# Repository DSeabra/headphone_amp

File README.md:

# headphone_amp
Guitar Headphone Amp

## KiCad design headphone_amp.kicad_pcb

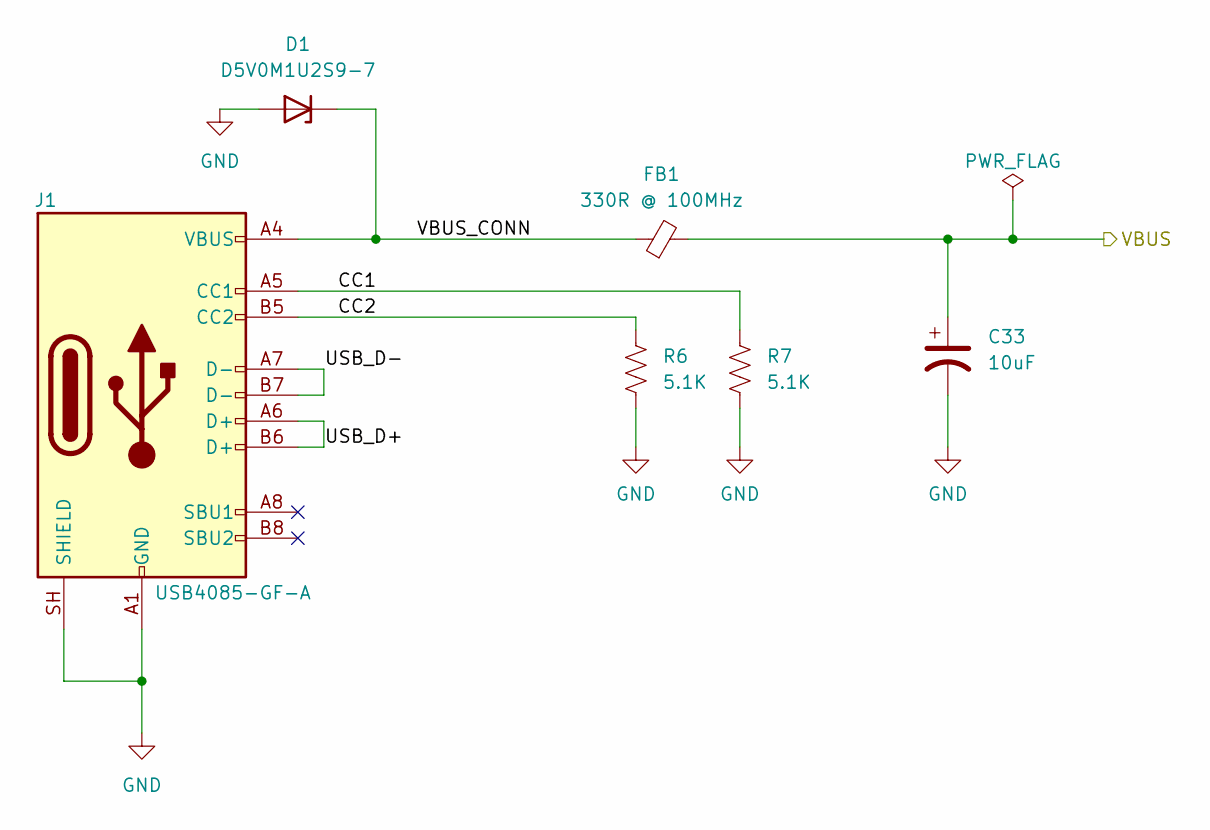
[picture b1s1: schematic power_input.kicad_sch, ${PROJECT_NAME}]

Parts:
C33: 10uF; TCJA_AVX
D1: D5V0M1U2S9-7; D_SOD-923
FB1: 330R @ 100MHz; L_0402_1005Metric
J1: USB4085-GF-A; USB_C_Receptacle_GCT_USB4085
R6, R7: 5.1K; R_0402_1005Metric

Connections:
/Power Input/CC1: J1.A5 (CC1), R7.1
/Power Input/CC2: J1.B5 (CC2), R6.1
/Power Input/USB_D+: J1.A6 (D+), J1.B6 (D+)
/Power Input/USB_D-: J1.A7 (D-), J1.B7 (D-)
/Power Input/VBUS_CONN: D1.1 (K), FB1.1, J1.A4 (VBUS), J1.A9 (VBUS), J1.B4 (VBUS), J1.B9 (VBUS)
/V_{BUS}: C33.1, FB1.2; also elsewhere on the board
GND: C33.2, D1.2 (A), J1.A1 (GND), J1.A12 (GND), J1.B1 (GND), J1.B12 (GND), J1.SH (SHIELD), R6.2, R7.2; also elsewhere on the board

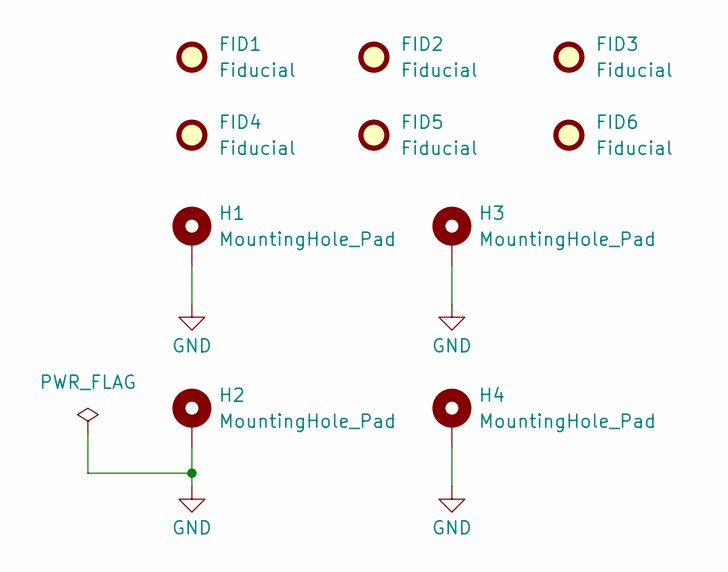
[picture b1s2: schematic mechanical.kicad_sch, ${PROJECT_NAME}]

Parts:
FID1, FID2, FID3, FID4, FID5, FID6: Fiducial; Fiducial_1.5mm_Mask3mm
H1, H2, H3, H4: MountingHole_Pad; MountingHole_3.2mm_M3_DIN965_Pad

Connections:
GND: H1.1 (1_1), H2.1 (1_1), H3.1 (1_1), H4.1 (1_1); also elsewhere on the board

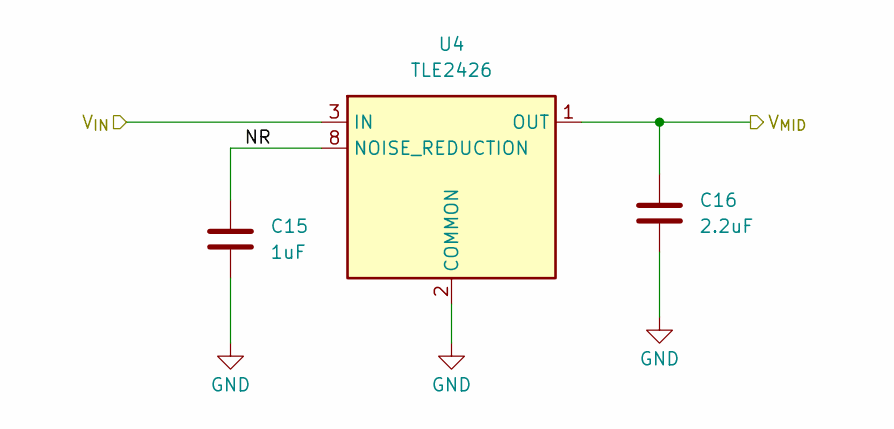
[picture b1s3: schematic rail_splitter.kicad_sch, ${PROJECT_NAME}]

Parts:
C15: 1uF; C_0603_1608Metric
C16: 2.2uF; C_0603_1608Metric
U4: TLE2426; SOIC-8_3.9x4.9mm_P1.27mm

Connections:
/Rail Splitter/NR: C15.2, U4.8 (NOISE_REDUCTION)
/V+: U4.3 (IN); also elsewhere on the board
/V_{MID}: C16.2, U4.1 (OUT); also elsewhere on the board
GND: C15.1, C16.1, U4.2 (COMMON); also elsewhere on the board

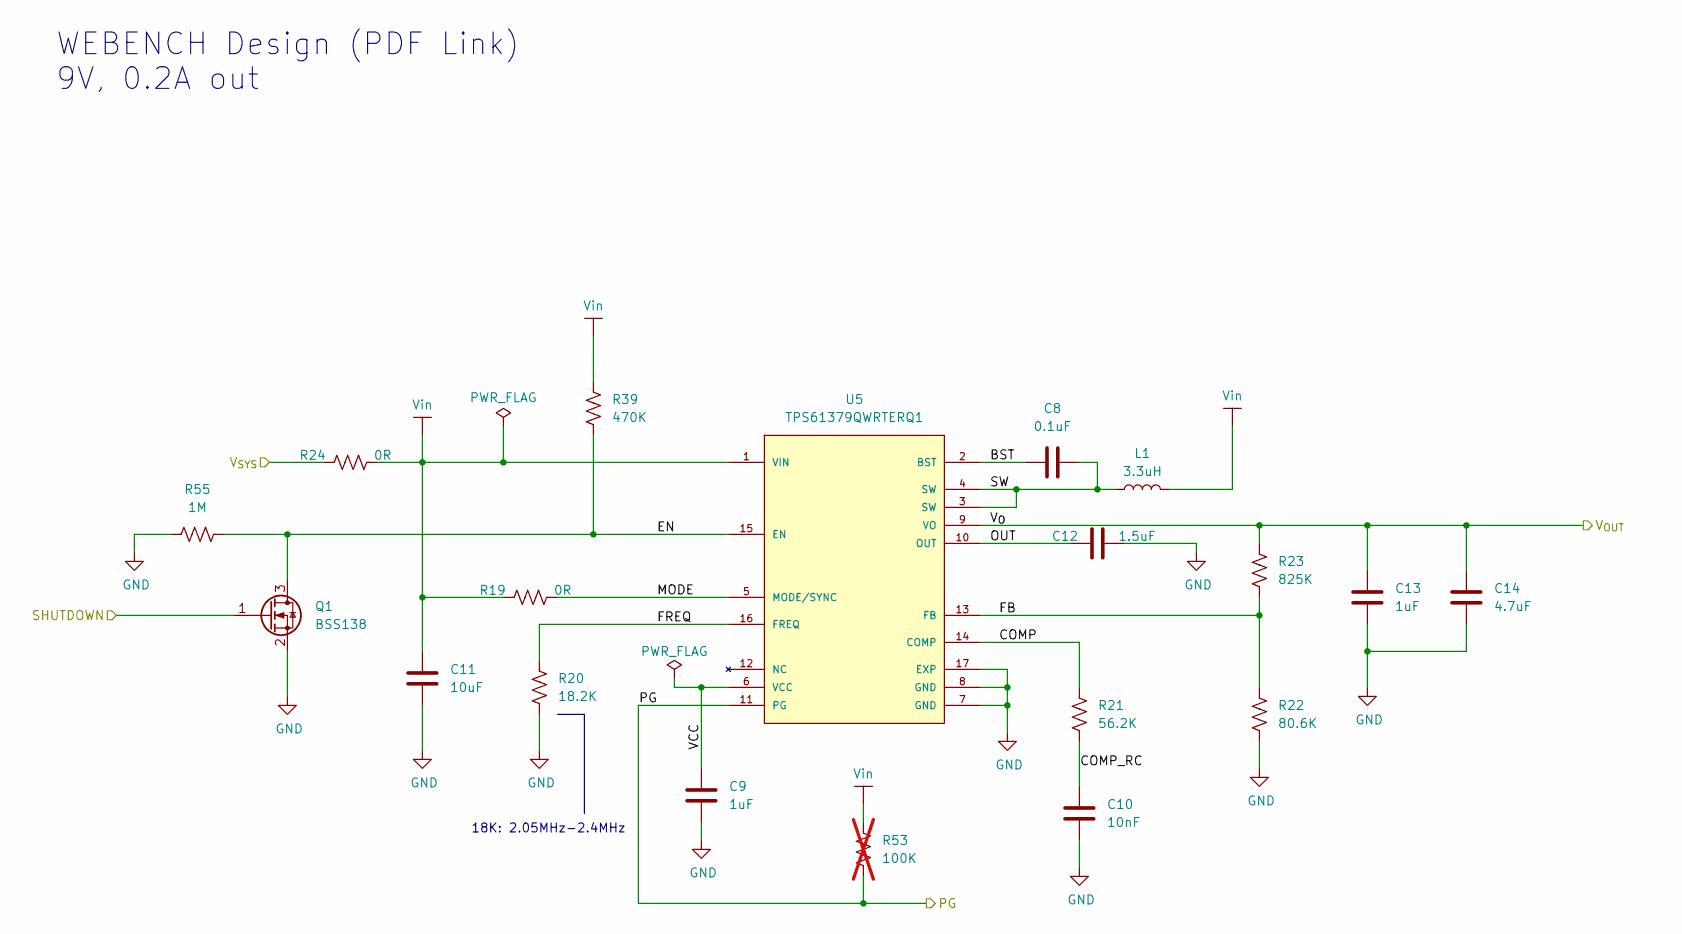
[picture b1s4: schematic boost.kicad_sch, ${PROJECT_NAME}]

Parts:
C8: 0.1uF; C_0402_1005Metric
C9, C13: 1uF; C_0402_1005Metric
C10: 10nF; C_0402_1005Metric
C11: 10uF; C_0805_2012Metric
C12: 1.5uF; C_0805_2012Metric
C14: 4.7uF; C_0603_1608Metric
L1: 3.3uH; L_1008_2520Metric
Q1: BSS138; SOT-23
R19, R24: 0R; R_0402_1005Metric
R20: 18.2K; R_0402_1005Metric
R21: 56.2K; R_0402_1005Metric
R22: 80.6K; R_0402_1005Metric
R23: 825K; R_0402_1005Metric
R39: 470K; R_0402_1005Metric
R53: 100K; R_0402_1005Metric; not fitted
R55: 1M; R_0402_1005Metric
U5: TPS61379QWRTERQ1; VREG_TPS61379QWRTERQ1

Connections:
/Boost/BST: C8.1, U5.2 (BST)
/Boost/COMP: R21.2, U5.14 (COMP)
/Boost/COMP_RC: C10.1, R21.1
/Boost/EN: Q1.3 (D), R39.2, R55.2, U5.15 (EN)
/Boost/FB: R22.2, R23.1, U5.13 (FB)
/Boost/FREQ: R20.2, U5.16 (FREQ)
/Boost/MODE: R19.2, U5.5 (MODE/SYNC)
/Boost/OUT: C12.1, U5.10 (OUT)
/Boost/PG: R53.1, U5.11 (PG); also elsewhere on the board
/Boost/SHUTDOWN: Q1.1 (G); also elsewhere on the board
/Boost/SW: C8.2, L1.1, U5.3 (SW), U5.4 (SW)
/Boost/VCC: C9.1, U5.6 (VCC)
/Boost/Vin: C11.2, L1.2, R19.1, R24.2, R39.1, R53.2, U5.1 (VIN)
/V+: C13.2, C14.2, R23.2, U5.9 (VO); also elsewhere on the board
/V_{SYS}: R24.1; also elsewhere on the board
GND: C9.2, C10.2, C11.1, C12.2, C13.1, C14.1, Q1.2 (S), R20.1, R22.1, R55.1, U5.7 (GND), U5.8 (GND), U5.17 (EXP); also elsewhere on the board

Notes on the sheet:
WEBENCH Design (PDF Link) 9V, 0.2A out
18K: 2.05MHz-2.4MHz

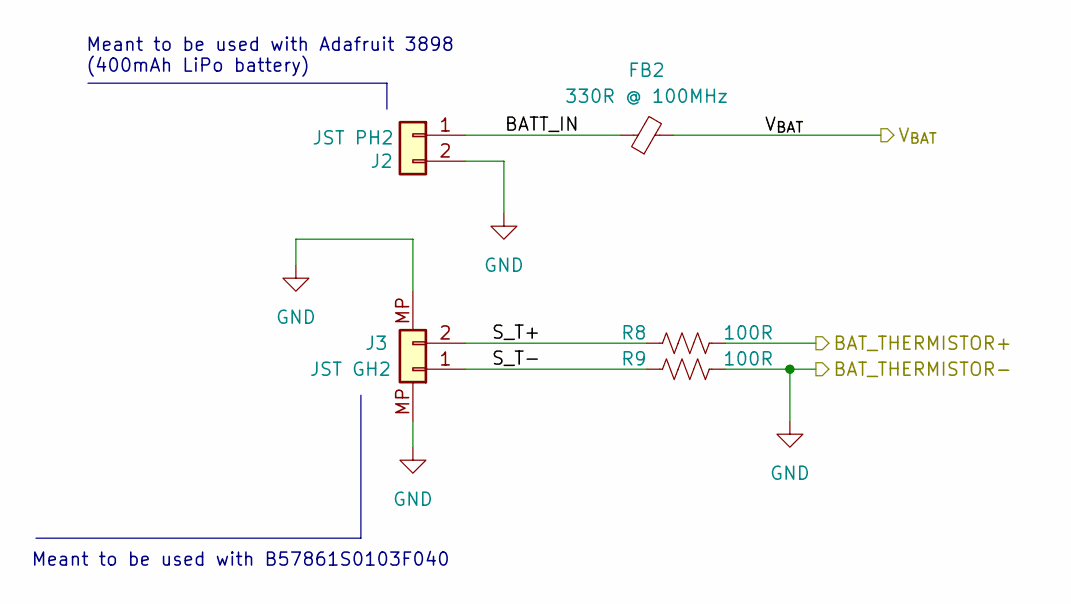
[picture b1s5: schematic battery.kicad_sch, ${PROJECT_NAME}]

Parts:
FB2: 330R @ 100MHz; L_0402_1005Metric
J2: JST PH2; JST_PH_S2B-PH-K_1x02_P2.00mm_Horizontal
J3: JST GH2; JST_GH_SM02B-GHS-TB_1x02-1MP_P1.25mm_Horizontal
R8, R9: 100R; R_0402_1005Metric

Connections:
/Battery Charger/TS+: R8.2; also elsewhere on the board
/Battery/BATT_IN: FB2.1, J2.1
/Battery/S_T+: J3.2, R8.1
/Battery/S_T-: J3.1, R9.1
/V_{BAT}: FB2.2; also elsewhere on the board
GND: J2.2, J3.MP, R9.2; also elsewhere on the board

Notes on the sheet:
Meant to be used with B57861S0103F040
Meant to be used with Adafruit 3898 (400mAh LiPo battery)

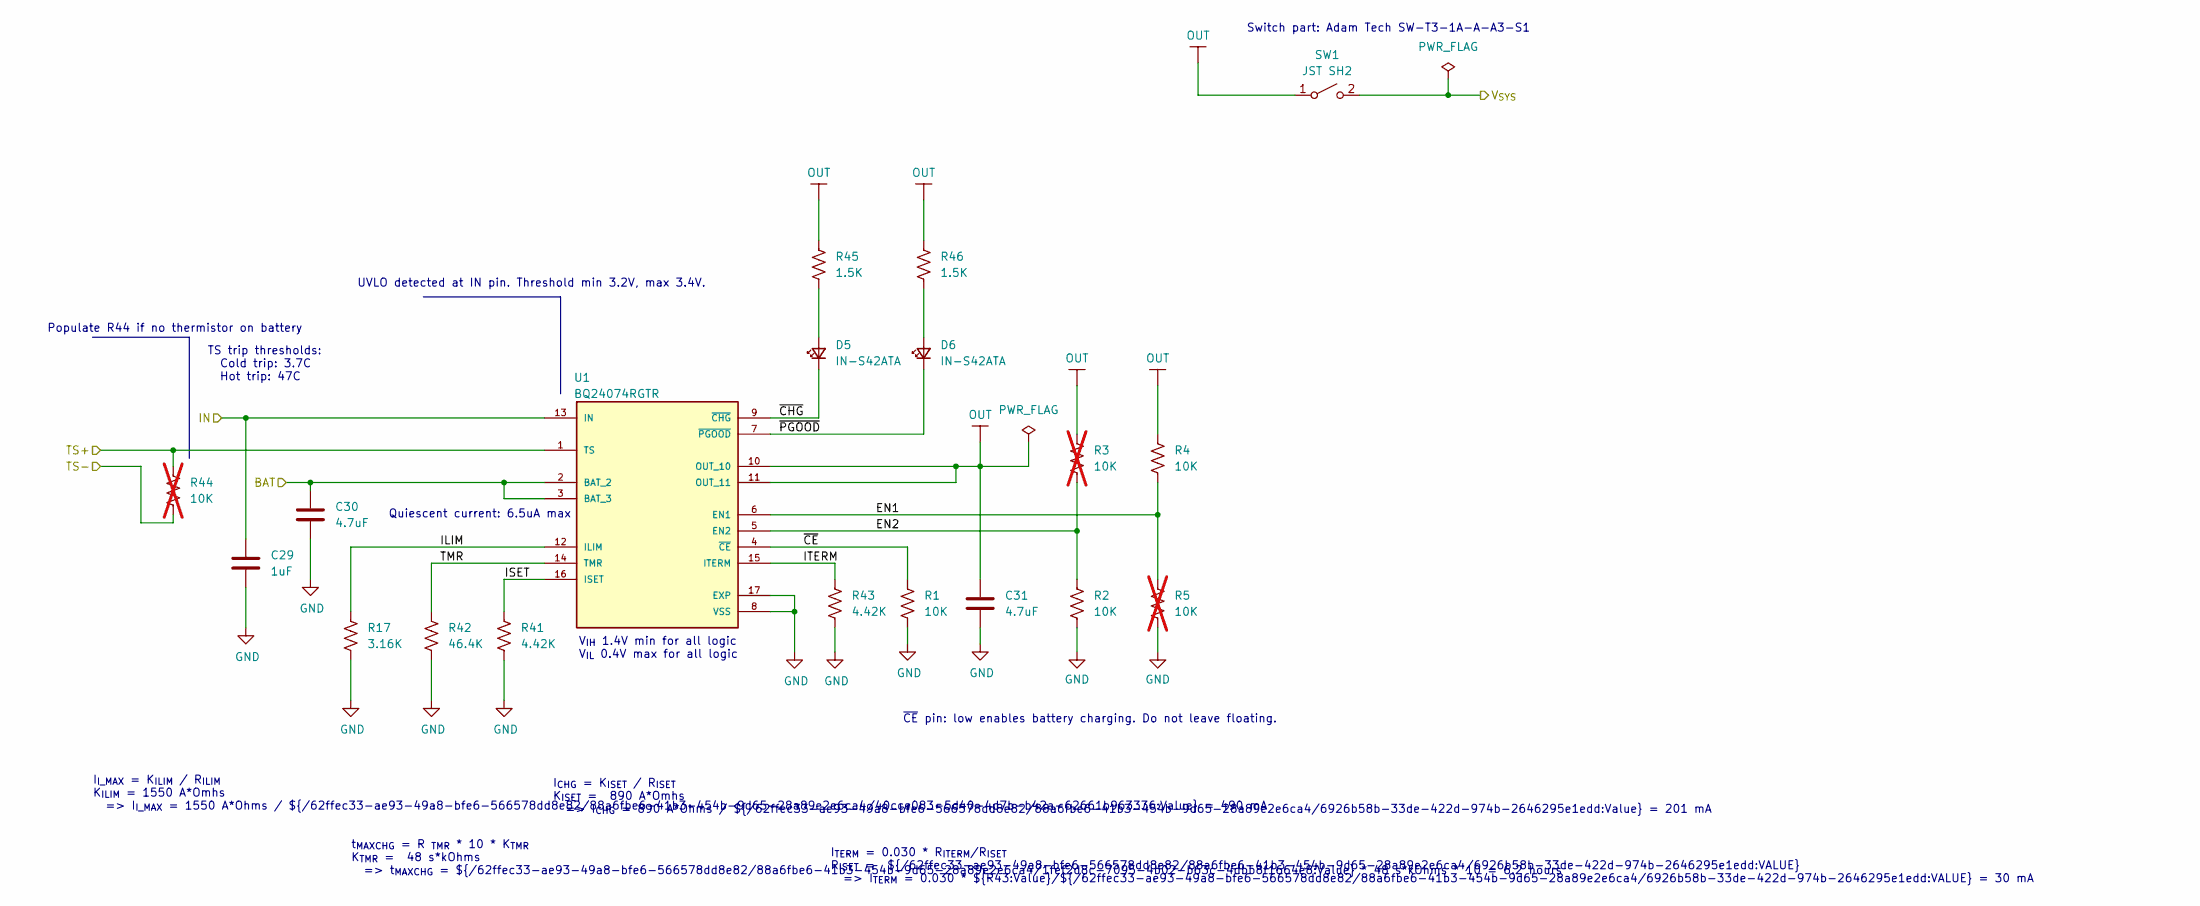
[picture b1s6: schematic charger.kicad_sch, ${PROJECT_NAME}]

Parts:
C29: 1uF; C_0402_1005Metric
C30, C31: 4.7uF; C_0603_1608Metric
D5, D6: IN-S42ATA; LED_0402_1005Metric
R1, R2, R4: 10K; R_0402_1005Metric
R3, R5, R44: 10K; R_0402_1005Metric; not fitted
R17: 3.16K; R_0402_1005Metric
R41, R43: 4.42K; R_0402_1005Metric
R42: 46.4K; R_0402_1005Metric
R45, R46: 1.5K; R_0402_1005Metric
SW1: JST SH2; JST_SH_BM02B-SRSS-TB_1x02-1MP_P1.00mm_Vertical
U1: BQ24074RGTR; bq24074rgtr

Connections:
/Battery Charger/EN1: R4.2, R5.1, U1.6 (EN1)
/Battery Charger/EN2: R2.1, R3.2, U1.5 (EN2)
/Battery Charger/ILIM: R17.1, U1.12 (ILIM)
/Battery Charger/ISET: R41.2, U1.16 (ISET)
/Battery Charger/ITERM: R43.2, U1.15 (ITERM)
/Battery Charger/OUT: C31.2, R3.1, R4.1, R45.2, R46.2, SW1.1 (A), U1.10 (OUT_10), U1.11 (OUT_11)
/Battery Charger/TMR: R42.2, U1.14 (TMR)
/Battery Charger/TS+: R44.1, U1.1 (TS); also elsewhere on the board
/Battery Charger/~CE: R1.1, U1.4 (~CE)
/Battery Charger/~CHG: D5.1 (K), U1.9 (~CHG)
/Battery Charger/~PGOOD: D6.1 (K), U1.7 (~PGOOD)
/V_{BAT}: C30.2, U1.2 (BAT_2), U1.3 (BAT_3); also elsewhere on the board
/V_{BUS}: C29.2, U1.13 (IN); also elsewhere on the board
/V_{SYS}: SW1.2 (B); also elsewhere on the board
GND: C29.1, C30.1, C31.1, R1.2, R2.2, R5.2, R17.2, R41.1, R42.1, R43.1, R44.2, U1.8 (VSS), U1.17 (EXP); also elsewhere on the board
unnamed: D5.2 (A), R45.1
unnamed: D6.2 (A), R46.1

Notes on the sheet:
~{CE} pin: low enables battery charging. Do not leave floating.
Quiescent current: 6.5uA max
V_{IH} 1.4V min for all logic V_{IL} 0.4V max for all logic
UVLO detected at IN pin. Threshold min 3.2V, max 3.4V.
I_{TERM} = 0.030 * R_{ITERM}/R_{ISET} R_{ISET} = ${/62ffec33-ae93-49a8-bfe6-566578dd8e82/88a6fbe6-41b3-454b-9d65-28a89e2e6ca4/6926b58b-33de-422d-974b-2646295e1edd:VALUE} => I_{TERM} = 0.030 * ${R43:Value}/${/62ffec33-ae93-49a8-bfe6-566578dd8e82/88a6fbe6-41b3-454b-9d65-28a89e2e6ca4/6926b58b-33de-422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
TS trip thresholds: Cold trip: 3.7C Hot trip: 47C
t_{MAXCHG} = R _{TMR} * 10 * K_{TMR} K_{TMR} = 48 s*kOhms => t_{MAXCHG} = ${/62ffec33-ae93-49a8-bfe6-566578dd8e82/88a6fbe6-41b3-454b-9d65-28a89e2e6ca4/1fef2d8c-7095-4b02-b63c-4dbb8f1664e8:Value} * 48 s*kOhms * 10 = 6.2 hours
Switch part: Adam Tech SW-T3-1A-A-A3-S1
I_{I_MAX} = K_{ILIM} / R_{ILIM} K_{ILIM} = 1550 A*Omhs => I_{I_MAX} = 1550 A*Ohms / ${/62ffec33-ae93-49a8-bfe6-566578dd8e82/88a6fbe6-41b3-454b-9d65-28a89e2e6ca4/40cce083-5d40-4d7b-b42a-62661b963336:Value} = 490 mA
Populate R44 if no thermistor on battery
I_{CHG} = K_{ISET} / R_{ISET} K_{ISET} = 890 A*Omhs => I_{CHG} = 890 A*Ohms / ${/62ffec33-ae93-49a8-bfe6-566578dd8e82/88a6fbe6-41b3-454b-9d65-28a89e2e6ca4/6926b58b-33de-422d-974b-2646295e1edd:Value} = 201 mA

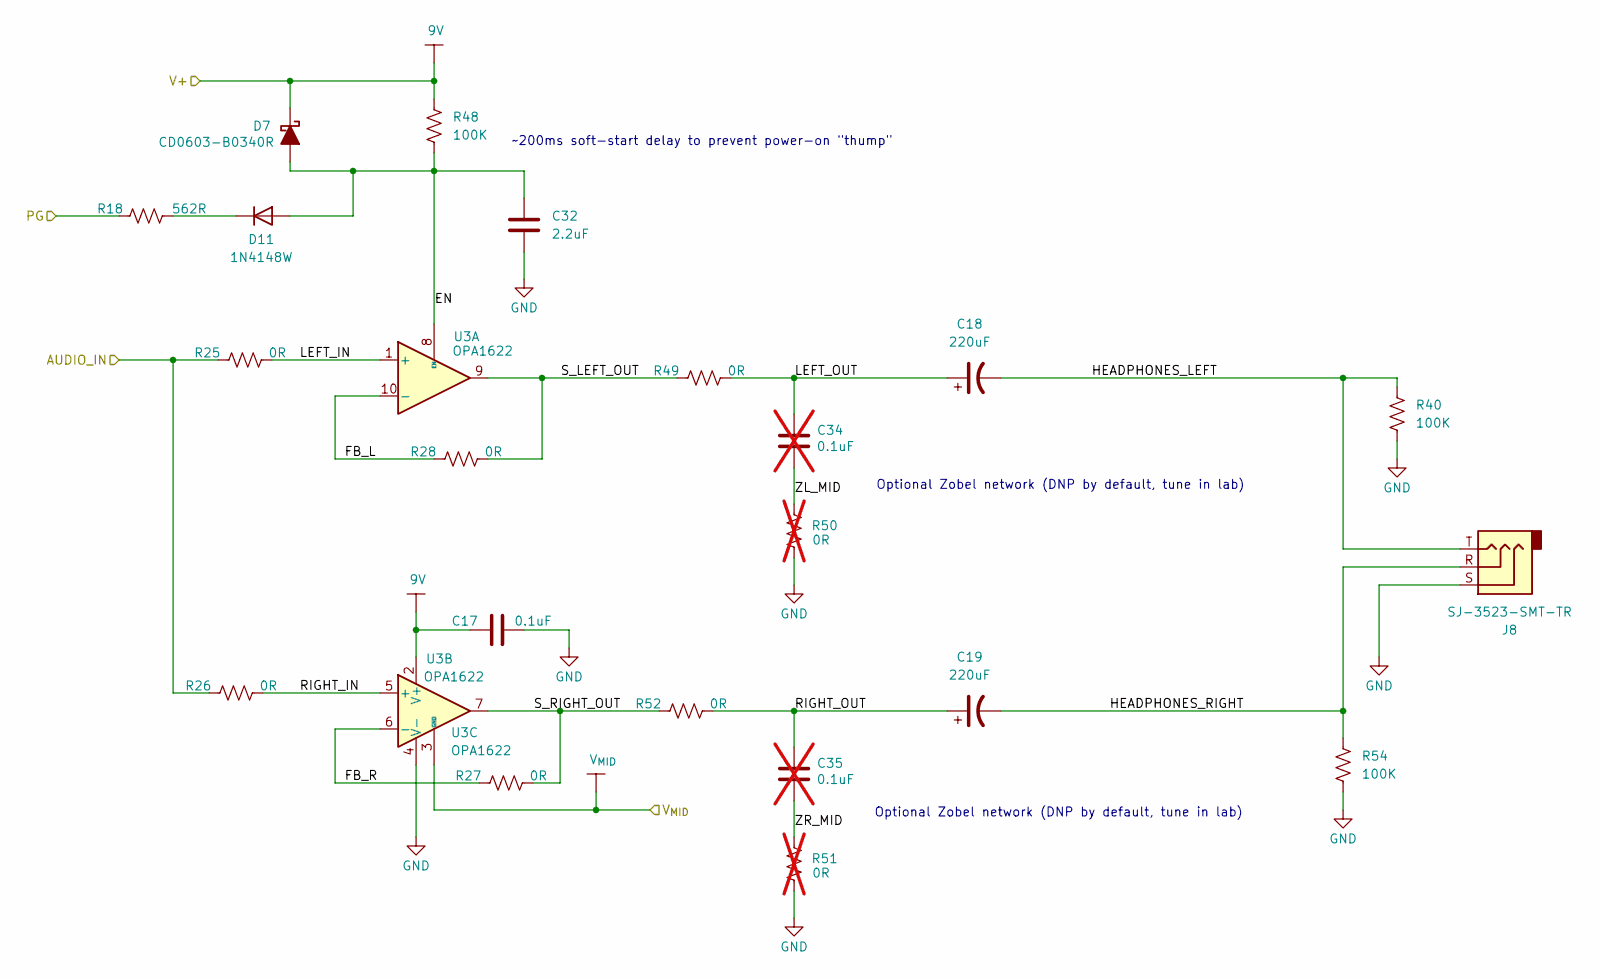
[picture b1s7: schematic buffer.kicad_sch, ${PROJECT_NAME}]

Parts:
C17: 0.1uF; C_0402_1005Metric
C18, C19: 220uF; WCAP-PSLP_6.3X5.8_DXL_
C32: 2.2uF; C_0603_1608Metric
C34, C35: 0.1uF; C_0402_1005Metric; not fitted
D7: CD0603-B0340R; D_0603_1608Metric
D11: 1N4148W; D_SOD-123
J8: SJ-3523-SMT-TR; Jack_3.5mm_CUI_SJ-3523-SMT_Horizontal
R18: 562R; R_0402_1005Metric
R25, R26, R27, R28, R49, R52: 0R; R_0402_1005Metric
R40, R48, R54: 100K; R_0402_1005Metric
R50, R51: 0R; R_0402_1005Metric; not fitted
U3: OPA1622; Texas_S-PVSON-N10

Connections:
/Audio Input/AUDIO_OUT: R25.1, R26.1; also elsewhere on the board
/Audio Output/EN: C32.2, D7.2 (A), D11.2 (A), R48.1, U3.8 (EN)
/Audio Output/FB_L: R28.1, U3.10 (-)
/Audio Output/FB_R: R27.1, U3.6 (-)
/Audio Output/HEADPHONES_LEFT: C18.2, J8.T, R40.1
/Audio Output/HEADPHONES_RIGHT: C19.2, J8.R, R54.1
/Audio Output/LEFT_IN: R25.2, U3.1 (+)
/Audio Output/LEFT_OUT: C18.1, C34.2, R49.2
/Audio Output/RIGHT_IN: R26.2, U3.5 (+)
/Audio Output/RIGHT_OUT: C19.1, C35.2, R52.2
/Audio Output/S_LEFT_OUT: R28.2, R49.1, U3.9
/Audio Output/S_RIGHT_OUT: R27.2, R52.1, U3.7
/Audio Output/ZL_MID: C34.1, R50.2
/Audio Output/ZR_MID: C35.1, R51.2
/Boost/PG: R18.1; also elsewhere on the board
/V+: C17.1, D7.1 (K), R48.2, U3.2 (V+); also elsewhere on the board
/V_{MID}: U3.3 (GND); also elsewhere on the board
GND: C17.2, C32.1, J8.S, R40.2, R50.1, R51.1, R54.2, U3.4 (V-), U3.11 (V-); also elsewhere on the board
unnamed: D11.1 (K), R18.2

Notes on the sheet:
Optional Zobel network (DNP by default, tune in lab)
~200ms soft-start delay to prevent power-on "thump"

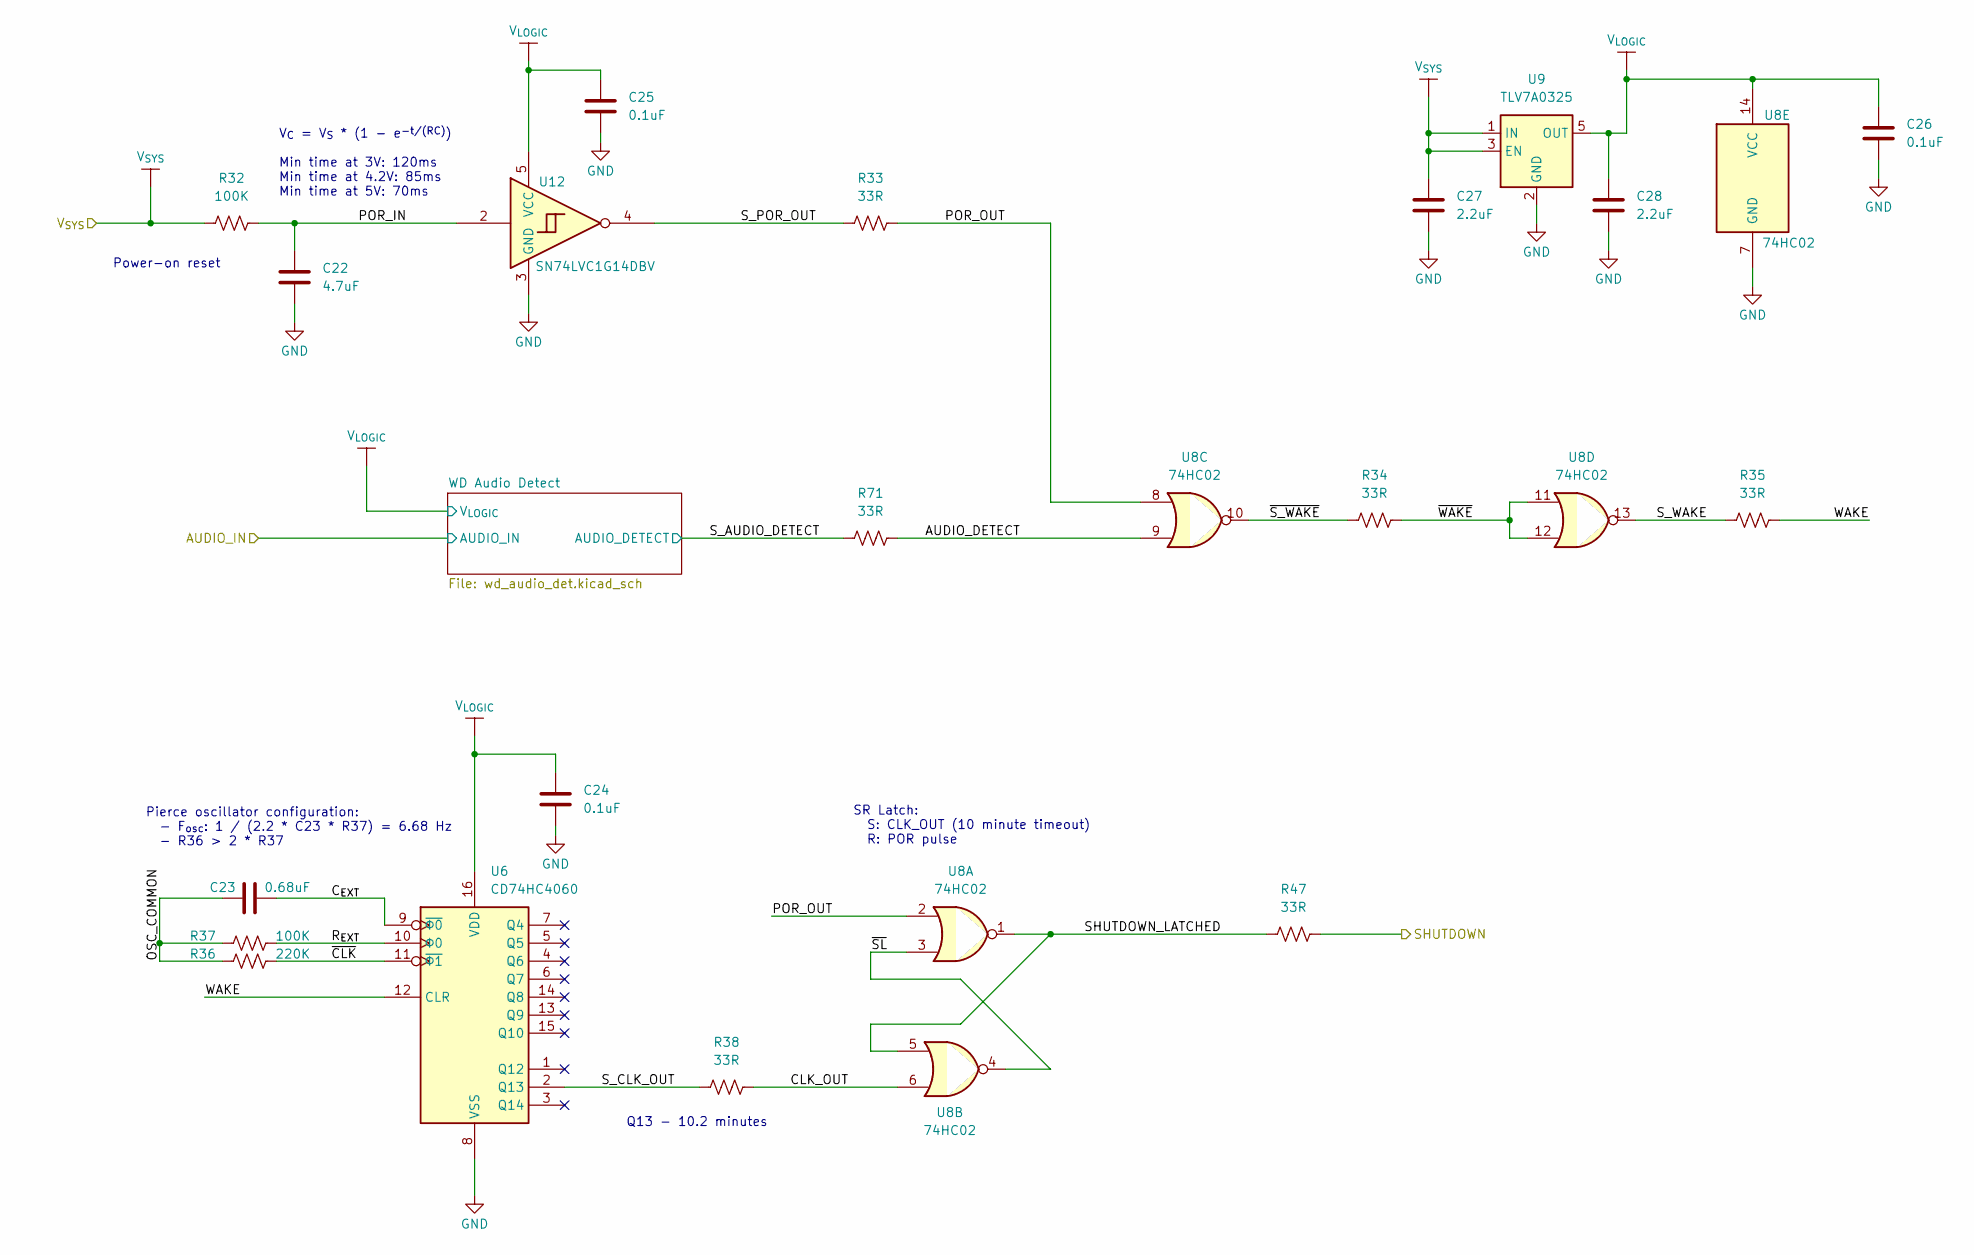
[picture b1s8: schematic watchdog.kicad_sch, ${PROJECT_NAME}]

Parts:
C22: 4.7uF; C_0603_1608Metric
C23: 0.68uF; C_0402_1005Metric
C24, C25, C26: 0.1uF; C_0402_1005Metric
C27, C28: 2.2uF; C_0603_1608Metric
R32, R37: 100K; R_0402_1005Metric
R33, R34, R35, R38, R47, R71: 33R; R_0402_1005Metric
R36: 220K; R_0402_1005Metric
U6: CD74HC4060; TSSOP-16_4.4x5mm_P0.65mm
U8: 74HC02; TSSOP-14_4.4x5mm_P0.65mm
U9: TLV7A0325; SOT-23-5
U12: SN74LVC1G14DBV; SOT-23-5

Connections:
/Boost/SHUTDOWN: R47.1; also elsewhere on the board
/V_{SYS}: C27.2, R32.1, U9.1 (IN), U9.3 (EN); also elsewhere on the board
/Watchdog/AUDIO_DETECT: R71.1, U8.9
/Watchdog/CLK_OUT: R38.1, U8.6
/Watchdog/C_{EXT}: C23.1, U6.9 (~Φ0)
/Watchdog/OSC_COMMON: C23.2, R36.2, R37.2
/Watchdog/POR_IN: C22.2, R32.2, U12.2
/Watchdog/POR_OUT: R33.1, U8.2, U8.8
/Watchdog/R_{EXT}: R37.1, U6.10 (Φ0)
/Watchdog/SHUTDOWN_LATCHED: R47.2, U8.1, U8.5
/Watchdog/S_AUDIO_DETECT: R71.2; also elsewhere on the board
/Watchdog/S_CLK_OUT: R38.2, U6.2 (Q13)
/Watchdog/S_POR_OUT: R33.2, U12.4
/Watchdog/S_WAKE: R35.2, U8.13
/Watchdog/V_{LOGIC}: C24.1, C25.1, C26.1, C28.2, U6.16 (VDD), U8.14 (VCC), U9.5 (OUT), U12.5 (VCC); also elsewhere on the board
/Watchdog/WAKE: R35.1, U6.12 (CLR)
/Watchdog/~CLK: R36.1, U6.11 (~Φ1)
/Watchdog/~SL: U8.3, U8.4
/Watchdog/~S_WAKE: R34.2, U8.10
/Watchdog/~WAKE: R34.1, U8.11, U8.12
GND: C22.1, C24.2, C25.2, C26.2, C27.1, C28.1, U6.8 (VSS), U8.7 (GND), U9.2 (GND), U12.3 (GND); also elsewhere on the board

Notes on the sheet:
Q13 - 10.2 minutes
Power-on reset
V_{C} = V_{S} * (1 - e^{-t/(RC)}) Min time at 3V: 120ms Min time at 4.2V: 85ms Min time at 5V: 70ms
Pierce oscillator configuration: - F_{osc}: 1 / (2.2 * C23 * R37) = 6.68 Hz - R36 > 2 * R37
SR Latch: S: CLK_OUT (10 minute timeout) R: POR pulse

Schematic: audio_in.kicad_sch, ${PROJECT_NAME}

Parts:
C1: 0.1uF; C_0402_1005Metric
FB3: 60R @ 2MHz; L_Wuerth_PMFI-201610
J5: Header_2x1; PinHeader_2x01_P2.54mm_Vertical; not fitted
J6: JST SH3; JST_SH_BM03B-SRSS-TB_1x03-1MP_P1.00mm_Vertical
J10: MJ-3523-SMT-TR; CONN_MJ-3523_CUD; not fitted
R56: 0R; R_0402_1005Metric; not fitted
U2: OPA1678; DRG0008A

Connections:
/Audio Input/AUDIO_OUT: J6.2; also elsewhere on the board
/Audio Input/CONDOR_INPUT: R56.1; also elsewhere on the board
/Audio Input/JACK_IN: J5.2, J10.2 (T); also elsewhere on the board
/Audio Input/RECOVERY_INPUT: R56.2; also elsewhere on the board
/Audio Input/RECOVERY_OUT: J6.3; also elsewhere on the board
/Audio Input/V_{+}F: C1.1, FB3.2, U2.8 (V+); also elsewhere on the board
/V+: FB3.1; also elsewhere on the board
/V_{MID}: J6.1; also elsewhere on the board
GND: C1.2, J5.1, J6.MP, J10.1 (S), U2.4 (V-), U2.9 (EP); also elsewhere on the board

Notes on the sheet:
Volume pot PN: PDB181-GTR01-103A2

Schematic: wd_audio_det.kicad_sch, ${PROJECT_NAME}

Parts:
C20: 1uF; C_0603_1608Metric
C21: 0.22uF; C_0402_1005Metric
C47: 1n; C_0402_1005Metric; not fitted
C48: 10n; R_0402_1005Metric
C49: 0.1uF; C_0402_1005Metric
D4: 1N4148W; D_SOD-123
R29, R30, R31: 470K; R_0402_1005Metric
R57: 220k; R_0402_1005Metric
R68: 30k; R_0402_1005Metric
R69: 0R; R_0402_1005Metric
R70: 4.7M; R_0402_1005Metric
U11: TLV7011; SOT-23-5

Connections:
/Audio Input/RECOVERY_OUT: C20.2; also elsewhere on the board
/Watchdog/S_AUDIO_DETECT: R70.2, U11.1; also elsewhere on the board
/Watchdog/V_{LOGIC}: C49.1, R57.1, U11.5 (V+); also elsewhere on the board
/Watchdog/WD Audio Detect/C_AUDIO_IN: C20.1, D4.2 (A), R29.2
/Watchdog/WD Audio Detect/ENV_HOLD: C21.1, D4.1 (K), R30.2
/Watchdog/WD Audio Detect/ENV_THRESHOLD: C47.1, R30.1, R31.1, R70.1, U11.3 (+)
/Watchdog/WD Audio Detect/RB_MID: R68.2, R69.1
/Watchdog/WD Audio Detect/VREF: C48.1, R57.2, R68.1, U11.4 (-)
GND: C21.2, C47.2, C48.2, C49.2, R29.1, R31.2, R69.2, U11.2 (V-); also elsewhere on the board

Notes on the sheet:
Threshold Adj Lab: Tune
Envelope Detector
Comparator

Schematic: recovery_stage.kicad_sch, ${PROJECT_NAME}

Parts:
C7: 470pF; C_0402_1005Metric
R14: 100K; R_0402_1005Metric
R15, R16: 33K; R_0402_1005Metric
U2: OPA1678; DRG0008A

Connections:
/Audio Input/RECOVERY_INPUT: R15.1; also elsewhere on the board
/Audio Input/RECOVERY_OUT: C7.2, R14.2, U2.7; also elsewhere on the board
/Audio Input/Recovery Stage/SECOND_STAGE+: R16.2, U2.5 (+)
/Audio Input/Recovery Stage/SECOND_STAGE_FB: C7.1, R14.1, R15.2, U2.6 (-)
/V_{MID}: R16.1; also elsewhere on the board

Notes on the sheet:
Av = -R14 / R15 => Av = -100K / 33K = -3.03x

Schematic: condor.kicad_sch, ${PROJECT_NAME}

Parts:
C36, C43, C45: 1n C0G; C_0603_1608Metric
C37: 0.1uF; C_0402_1005Metric
C38: 15n C0G; C_0603_1608Metric
C39: 10u X5R 25V; C_0805_2012Metric
C40: 1u X7R; C_0603_1608Metric; not fitted
C41: 47n C0G; C_0603_1608Metric
C42: 47n C0G; C_0805_2012Metric
C44, C46: 3n9 C0G; C_0603_1608Metric
R58, R59, R60, R67: 100K; R_0402_1005Metric
R61: 18k; R_0402_1005Metric
R62, R63, R64, R65: 22k; R_0402_1005Metric
R66: 100R; R_0402_1005Metric
U10: OPA1679IPW; TSSOP-14_4.4x5mm_P0.65mm

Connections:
/Audio Input/CONDOR_INPUT: C36.1, R58.2; also elsewhere on the board
/Audio Input/Condor Cab Sim/BT_MID: C38.1, R58.1, R59.2, R67.2
/Audio Input/Condor Cab Sim/BT_OUT: C36.2, R59.1, U10.3 (+)
/Audio Input/Condor Cab Sim/HP_A: C41.2, C42.1, R61.1
/Audio Input/Condor Cab Sim/HP_B: C42.2, R60.1, U10.12 (+)
/Audio Input/Condor Cab Sim/HP_OUT: R61.2, R62.1, U10.13 (-), U10.14
/Audio Input/Condor Cab Sim/LP1_A: C44.1, R62.2, R63.1
/Audio Input/Condor Cab Sim/LP1_B: C43.1, R63.2, U10.10 (+)
/Audio Input/Condor Cab Sim/LP1_OUT: C44.2, R64.1, U10.8, U10.9 (-)
/Audio Input/Condor Cab Sim/LP2_A: C46.1, R64.2, R65.1
/Audio Input/Condor Cab Sim/LP2_B: C45.1, R65.2, U10.5 (+)
/Audio Input/Condor Cab Sim/LP2_OUT: C46.2, R66.1, U10.6 (-), U10.7
/Audio Input/Condor Cab Sim/NOTCH_OUT: C41.1, U10.1, U10.2 (-)
/Audio Input/RECOVERY_INPUT: R66.2; also elsewhere on the board
/Audio Input/V_{+}F: C37.1, C39.1, U10.4 (V+); also elsewhere on the board
/V_{MID}: C38.2, C40.1, C43.2, C45.2, R60.2, R67.1; also elsewhere on the board
GND: C37.2, C39.2, C40.2, U10.11 (V-); also elsewhere on the board

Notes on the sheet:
STAGES (runoffgroove Condor, JFET gain stage omitted): R58/R59/R18 + C36/C38(+C21): bridged-T notch ~400 Hz (Jensen P10R dip); R18 also gives the +6 dB HF shelf and biases U10A. C41/C42/R60/R61 + U10B: Sallen-Key HP, f0 ~80 Hz, Q 1.18 (cab low-end rolloff + ~95 Hz bump). R62-R65/C43-C46 + U10C/U10D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
BUILD OPTIONS: Notch depth: stock C36 1n / C38 15n. Shallower: 1n5 / 10n. Much shallower (Marshall): 2n2 / 6n8. Marshall voicing: + R61 12k, R60 120k, R62-R65 16k (15k/18k), C44/C46 4n7. Bass: C41/C42 56n-68n more, 33n-39n less. Treble: R62-R65 18k more, 27k less. U10 alt: OPA4197IPW (same pinout, 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

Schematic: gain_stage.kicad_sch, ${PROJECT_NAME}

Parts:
C2, C6: 0.1uF; C_1210_3225Metric
C3: 470pF; C_0402_1005Metric
C4: 51pF; C_0402_1005Metric
C5: 47nF; C_0402_1005Metric
D3, D8, D9, D10: 1N4148W; D_SOD-123
J4: JST SH3; JST_SH_BM03B-SRSS-TB_1x03-1MP_P1.00mm_Vertical
JP1, JP2: SolderJumper_2_Open; SolderJumper-2_P1.3mm_Open_TrianglePad1.0x1.5mm
R10: 1K; R_0402_1005Metric
R11: 51K; R_0402_1005Metric
R12: 4.7K; R_0402_1005Metric
R13: 1M; R_0402_1005Metric
U2: OPA1678; DRG0008A

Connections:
/Audio Input/CONDOR_INPUT: C6.2; also elsewhere on the board
/Audio Input/Gain Stage/FB_AC_COUPLE: C5.1, R12.2
/Audio Input/Gain Stage/FB_RES: J4.1, R11.2
/Audio Input/Gain Stage/FIRST_STAGE_FB: C4.1, D8.1 (K), D9.2 (A), R11.1, R12.1, U2.2 (-)
/Audio Input/Gain Stage/FIRST_STAGE_IN: C2.2, R13.2, U2.3 (+)
/Audio Input/Gain Stage/FIRST_STAGE_OUT: C4.2, C6.1, D3.2 (A), D10.1 (K), J4.2, J4.3, JP1.2 (B), JP2.2 (B), U2.1
/Audio Input/Gain Stage/JACK_LPF: C2.1, C3.1, R10.2
/Audio Input/JACK_IN: R10.1; also elsewhere on the board
/V_{MID}: C5.2, R13.1; also elsewhere on the board
GND: C3.2, J4.MP; also elsewhere on the board
unnamed: D3.1 (K), D8.2 (A), JP2.1 (A)
unnamed: D9.1 (K), D10.2 (A), JP1.1 (A)

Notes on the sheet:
Av = 1 + (R11 + R_pot) / R12 Av_min (R_pot = 0): => Av_min = 1 + 51K/4.7K = 11.9x (21.5 dB) Av_max (R_pot = 500K): => Av_max = 1 + (51K + 500K)/4.7K = 118.2x (41.5 dB)
AC-Coupling Cap: Choose Film!
Gain pot PN: PDB181-GTR02-504A2
PN: CB027D0104JBA

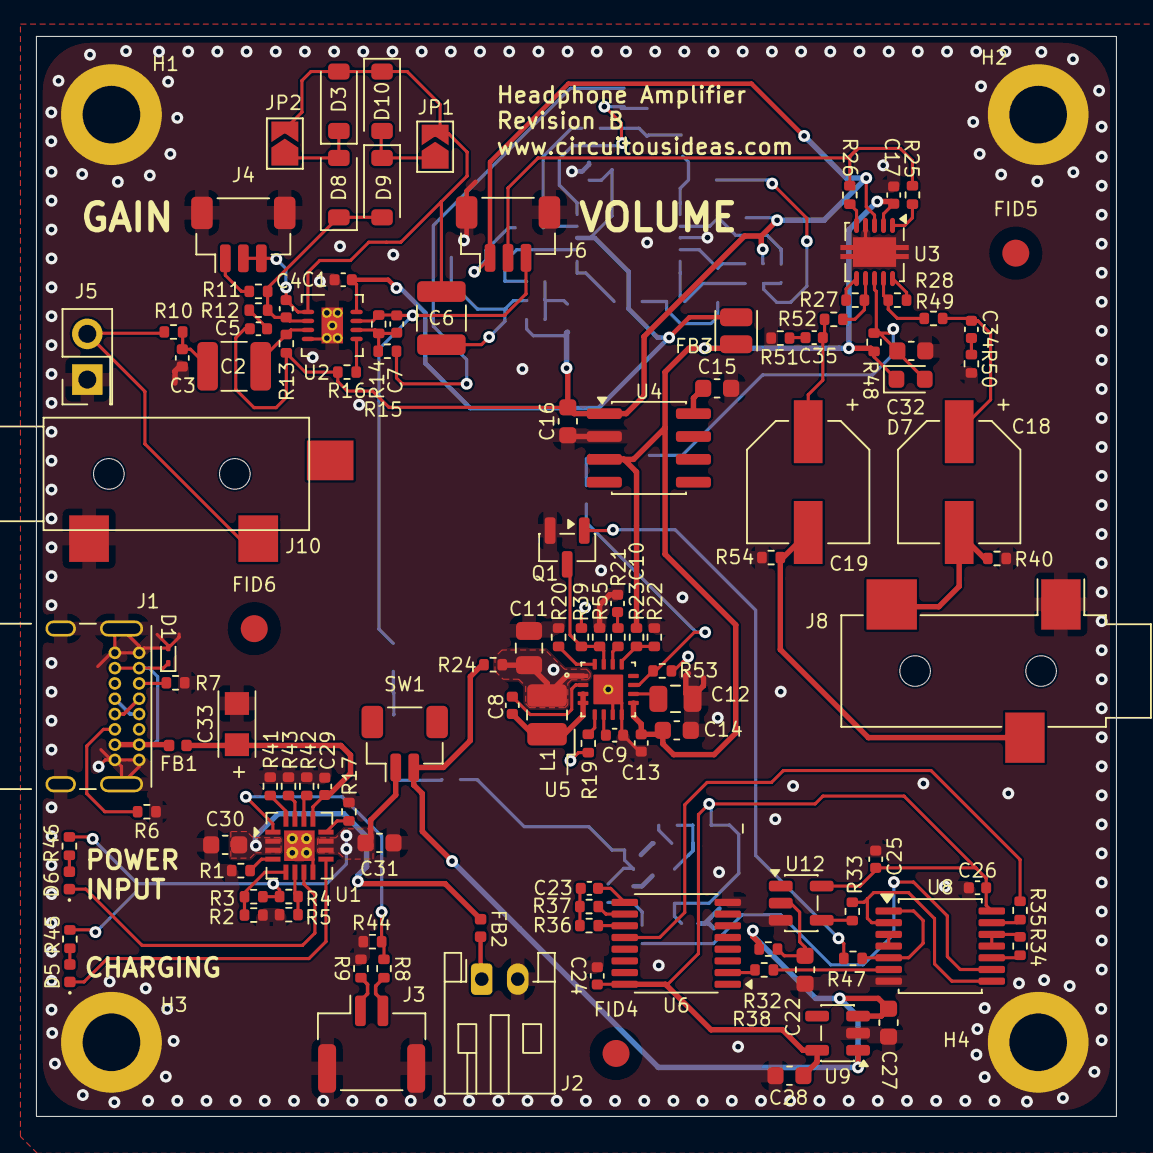
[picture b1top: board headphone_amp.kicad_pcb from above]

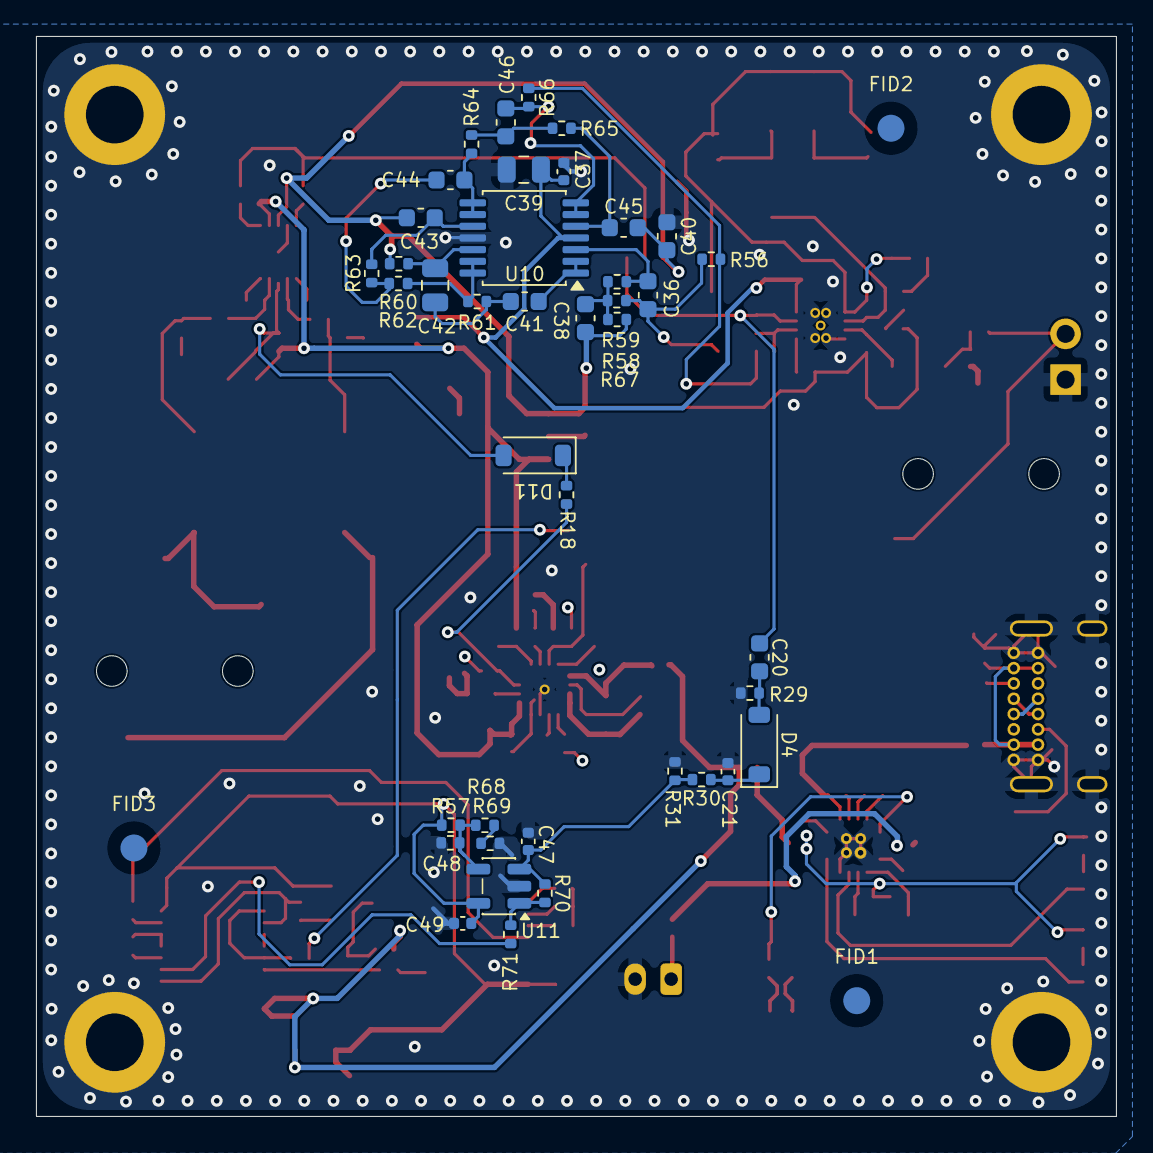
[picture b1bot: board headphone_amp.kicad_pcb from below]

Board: 4 copper layers, 60.0 x 60.0 mm, 167 parts (43 on the bottom side), 106 nets.

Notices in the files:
breakouts/condor_insert/condor_insert/condor_insert.kicad_sch:
After runoffgroove.com Condor (CC BY-NC-SA 3.0); JFET stage omitted, filters per Gringo BOM V0.6
